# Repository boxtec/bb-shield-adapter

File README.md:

# bb-shield-adapter
Breadboard Shield Adapter

[Product page Breadboard Shield Adapter](http://shop.boxtec.ch/breadboard-shield-adapter-kit-v10-p-42629.html)

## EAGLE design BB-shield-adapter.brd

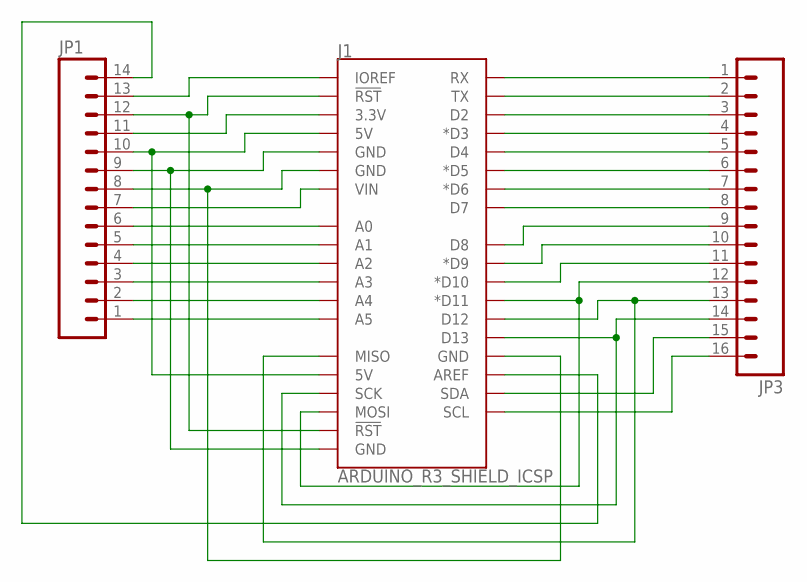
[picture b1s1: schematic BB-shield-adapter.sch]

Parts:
J1: ARDUINO_R3_SHIELD_ICSP; UNO_R3_SHIELD_ICSP
JP1: M14; 1X14
JP3: M16PTH; 1X16

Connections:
unnamed: J1.A5, JP1.1
unnamed: J1.A4, JP1.2
unnamed: J1.A3, JP1.3
unnamed: J1.A2, JP1.4
unnamed: J1.A1, JP1.5
unnamed: J1.A0, JP1.6
unnamed: J1.VIN, JP1.7
unnamed: J1.GND@1 (GND), J1.GND@2 (GND), JP1.8
unnamed: J1.GND@0 (GND), J1.GND_ICSP (GND), JP1.9
unnamed: J1.5V, J1.5V_ICSP (5V), JP1.10
unnamed: J1.3.3V, JP1.11
unnamed: J1.RES (!RST!), J1.RST_ICSP (!RST!), JP1.12
unnamed: J1.IOREF, JP1.13
unnamed: J1.RX, JP3.1
unnamed: J1.TX, JP3.2
unnamed: J1.D2, JP3.3
unnamed: J1.D3 (*D3), JP3.4
unnamed: J1.D4, JP3.5
unnamed: J1.D5 (*D5), JP3.6
unnamed: J1.D6 (*D6), JP3.7
unnamed: J1.D7, JP3.8
unnamed: J1.D8, JP3.9
unnamed: J1.D9 (*D9), JP3.10
unnamed: J1.D10 (*D10), JP3.11
unnamed: J1.D11 (*D11), J1.MOSI, JP3.12
unnamed: J1.D12, J1.MISO, JP3.13
unnamed: J1.D13, J1.SCK, JP3.14
unnamed: J1.AREF, JP1.14
unnamed: J1.SDA, JP3.15
SCL: J1.SCL, JP3.16

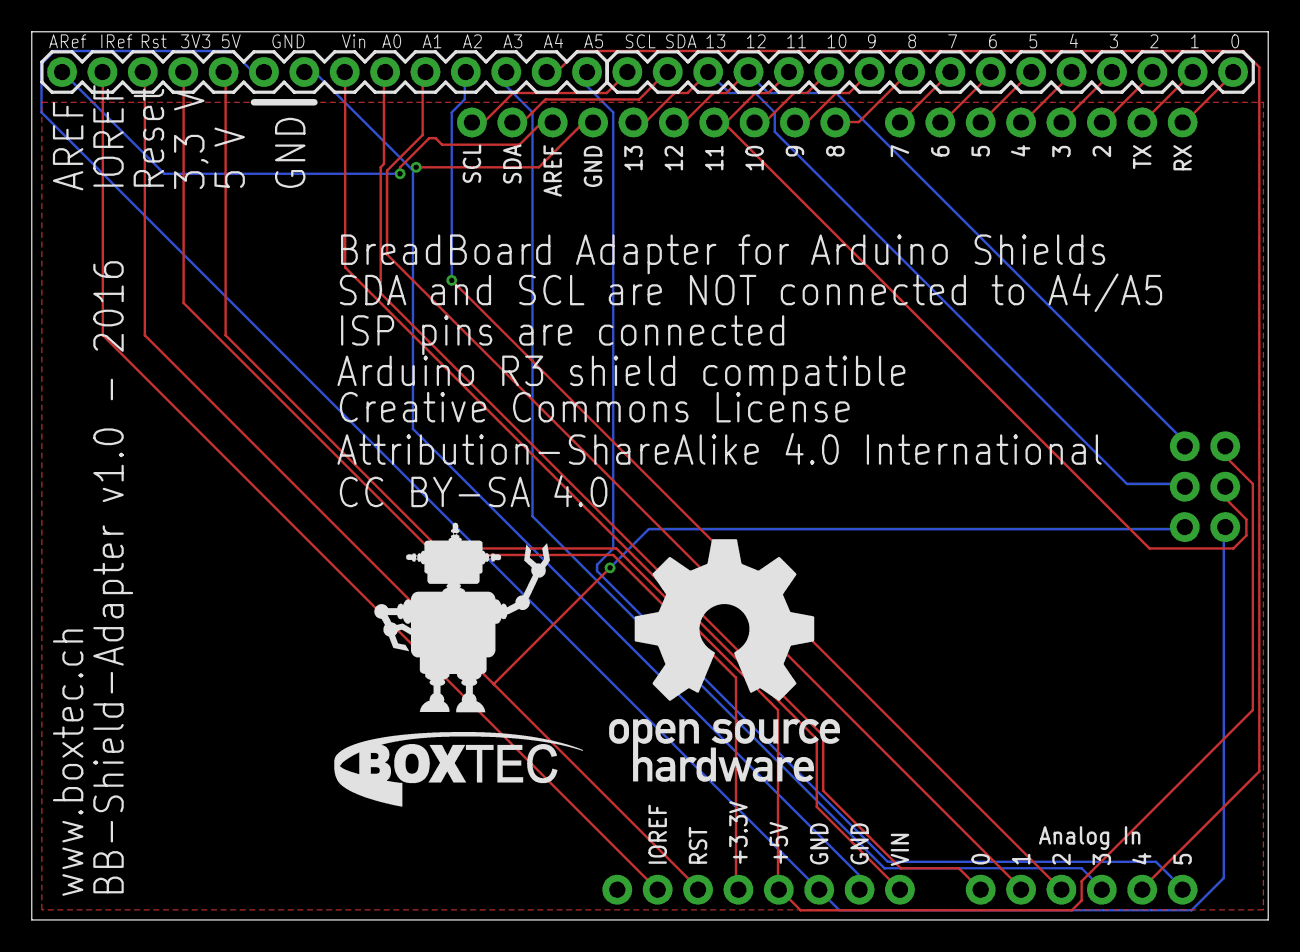
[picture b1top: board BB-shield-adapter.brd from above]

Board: 2 copper layers, 77.8 x 55.9 mm, 4 parts (0 on the bottom side), 30 nets.

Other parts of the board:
U$1: ROBOXTEC-LOGO-LARGE

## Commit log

2016-07-26 Initial git import

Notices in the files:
BB-shield-adapter.brd:
Creative Commons License
CC BY-SA 4.0
parts and their libraries:
SparkFun-Boards: Licensing: Creative Commons ShareAlike 4.0 International - https://creativecommons.org/licenses/by-sa/4.0
